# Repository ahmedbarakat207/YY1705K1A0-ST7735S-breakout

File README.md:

# YY1705K1A0 ST7735S 1-Layer Breakout & Driver Library

An open-source, **1-layer single-sided PCB breakout board** and **high-performance C++ driver** for the **YY1705K1A0** 1.8-inch TFT LCD SPI display (ST7735S controller, 128×160 RGB).

---

## Features

- **100% Single-Sided (1-Layer F.Cu)**: Designed specifically for home etching (toner transfer / photoresist). Zero jumpers or bottom vias required.
- **Through-Hole Passives (no SMD soldering)**: R1, R2, R3, C1, C2 are all standard through-hole parts — solder them with any basic iron. The only SMD part is the J2 FPC ZIF connector (required by the display flex cable).
- **Zero DRC Violations**: Optimized trace widths (0.35 mm signals, 0.60 mm power/GND) with 0.30 mm minimum clearances.
- **Clean Silkscreen**: Professional component labeling with open routing corridors.
- **Header-Only C++ Driver (`YY1705K1A0.h`)**:
  - Hardware SPI (fast DMA-capable) and Software bit-bang SPI constructors.
  - Complete 23-color RGB565 palette + `TFT_COLOR(r,g,b)` macro.
  - Fast graphic primitives (pixels, lines, rects, rounded rects, circles, triangles).
  - Built-in 5×7 ASCII font with scaling and Arduino `Print` interface (`print`/`println`).
  - Pre-built UI widgets (`drawProgressBar`).
  - Native support for display sleep, vertical scrolling, rotation (0°–270°), and partial mode.

---

## Hardware Overview

| Parameter | Specification |
|---|---|
| **Display Model** | YY1705K1A0 (1.8" TFT, 128×160) |
| **Driver IC** | Sitronix ST7735S |
| **Board Dimensions** | 34.0 mm × 53.0 mm |
| **Layers** | 1-Layer (Top Copper `F.Cu` Only) |
| **Interface** | 4-Wire SPI (3.3V Logic) |
| **Connectors** | `J1`: 7-Pin 2.54mm Header, `J2`: 12-Pin 0.5mm FPC |

---

## Pinout & Wiring

> **IMPORTANT**: This board and display operate strictly on **3.3V logic**. When interfacing with 5V microcontrollers (e.g. Arduino Uno / Mega), use a logic level shifter.

| J1 Pin | Label | Function | FPC Pin (J2) | MCU Connection (e.g., ESP32 / Arduino) |
|:---:|:---:|---|:---:|---|
| **1** | `+3V3` | +3.3V Power Supply | Pin 10 (`VDD`) | 3.3V Power Out |
| **2** | `GND` | Ground | Pins 2, 4, 11 | GND |
| **3** | `RST` | Reset (Active LOW) | Pin 5 (`RES`) | GPIO (e.g., D8) |
| **4** | `DC` | Data / Command Select | Pin 6 (`A0`) | GPIO (e.g., D9) |
| **5** | `MOSI` | SPI Data (SDA) | Pin 7 (`SDA`) | SPI MOSI (e.g., D11 / GPIO 23) |
| **6** | `SCK` | SPI Clock (SCL) | Pin 8 (`SCL`) | SPI SCK (e.g., D13 / GPIO 18) |
| **7** | `CS` | Chip Select (Active LOW) | Pin 9 (`CS`) | GPIO (e.g., D10 / GPIO 5) |

---

## Bill of Materials (BOM)

| Designator | Description | Package / Footprint | Quantity |
|---|---|---|:---:|
| **J1** | 7-Pin 2.54mm Header Male/Female | 1×07 Pin Header (0.1") THT | 1 |
| **J2** | 12-Pin 0.5mm Pitch Bottom-Contact FPC Connector | SMD 12-Pin 0.5mm **(only SMD part)** | 1 |
| **R1** | 22 Ω Backlight Current Limiter | Axial 1/4W THT, 7.62mm pitch (lying flat) | 1 |
| **R2, R3** | 10 kΩ Pull-up Resistors (`RESET`, `CS`) | Axial 1/4W THT, 5.08mm pitch (vertical mount) | 2 |
| **C1** | 10 µF 10V Ceramic/Electrolytic (Bulk Decoupling) | Disc/Radial THT, 5mm pitch | 1 |
| **C2** | 100 nF (0.1 µF) Ceramic Disc (HF Bypass) | Disc THT, 5mm pitch | 1 |

---

## Quick Start (Arduino / PlatformIO)

### Installation

1. Copy `YY1705K1A0.h` into your Arduino sketch folder or PlatformIO project `include/` directory.
2. In your sketch:

```cpp
#include <SPI.h>
#include "YY1705K1A0.h"

// Define pins
#define TFT_CS    10
#define TFT_DC    9
#define TFT_RST   8

// Hardware SPI instance (Fastest)
YY1705K1A0 tft(TFT_CS, TFT_DC, TFT_RST);

void setup() {
    // Initialize display with standard black-tab profile
    tft.begin(INITR_BLACKTAB);
    tft.fillScreen(TFT_BLACK);

    // Print text
    tft.setTextColor(TFT_WHITE, TFT_BLACK);
    tft.drawString(10, 20, "Hello World!", TFT_YELLOW, TFT_BLACK, 2);

    // Draw UI shapes
    tft.drawRoundRect(10, 60, 108, 30, 4, TFT_CYAN);
    tft.drawProgressBar(10, 100, 108, 14, 75, TFT_GREEN, TFT_DARKGREY, TFT_WHITE);
}

void loop() {
}
```

---

## DIY PCB Fabrication (Toner Transfer)

Print-ready vector PDF files scaled at 1:1 for DIY etching:

- **[YY1705K1A0_breakout_scaled_landscape.pdf](YY1705K1A0_breakout_scaled_landscape.pdf)**: 2 scaled boards per A4 page.
- **[YY1705K1A0_breakout_scaled_landscape_mirrored.pdf](YY1705K1A0_breakout_scaled_landscape_mirrored.pdf)**: Mirrored for direct iron-on toner transfer.

> **Printing Note**: Print with **Scale: 100% / Actual Size** enabled in your PDF viewer.

---

## Repository Structure

```
├── README.md                                          # Project documentation
├── LICENSE                                            # MIT Open-Source License
├── library.properties                                 # Arduino Library descriptor
├── library.json                                       # PlatformIO Library descriptor
├── YY1705K1A0.h                                       # Display driver header library
├── YY1705K1A0_breakout.kicad_pro                      # KiCad project file
├── YY1705K1A0_breakout.kicad_sch                      # KiCad schematic
├── YY1705K1A0_breakout.kicad_pcb                      # KiCad 1-layer PCB layout
├── BOM.csv                                            # Bill of Materials
├── display_connector_pinout.csv                       # FPC 12-pin reference sheet
├── WIRING_GUIDE.md                                    # Detailed wiring instructions
├── YY1705K1A0_breakout_scaled_landscape.pdf           # Printable A4 etching mask
├── YY1705K1A0_breakout_scaled_landscape_mirrored.pdf  # Mirrored etching mask
└── examples/
    └── GraphicTest/
        └── GraphicTest.ino                            # Complete demo sketch
```

---

## License

This project is open-source hardware and software licensed under the [MIT License](LICENSE).

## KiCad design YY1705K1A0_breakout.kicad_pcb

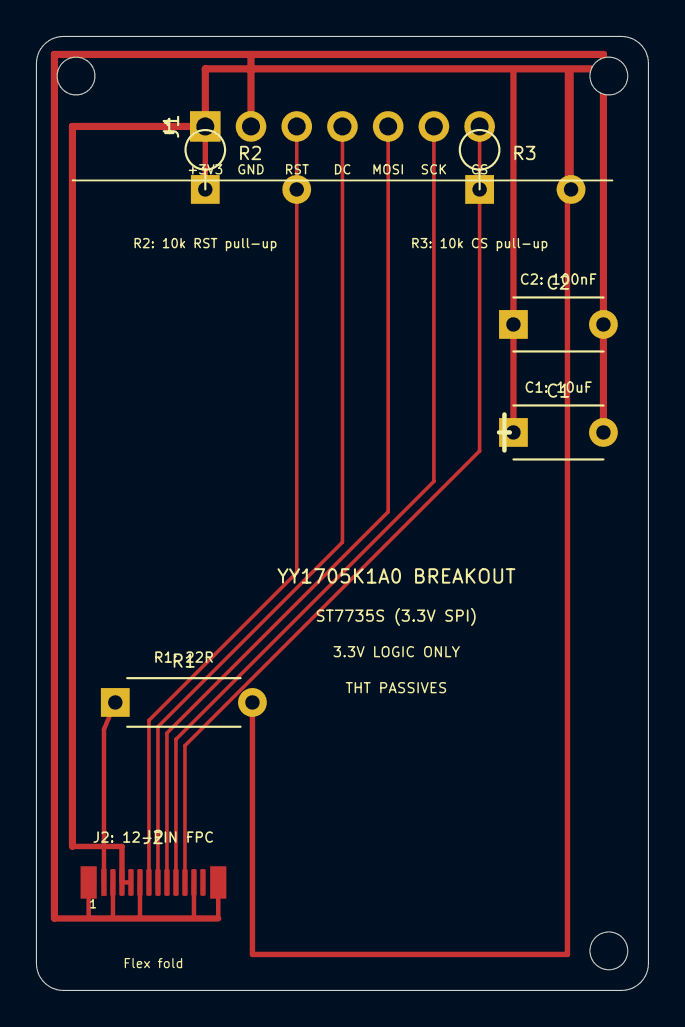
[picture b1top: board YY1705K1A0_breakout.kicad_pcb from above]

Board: 2 copper layers, 34.0 x 53.0 mm, 10 parts (0 on the bottom side), 8 nets.

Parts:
C1: 10uF; C_Disc_D5.0mm_W2.5mm_P5.00mm
C2: 100nF; C_Disc_D5.0mm_W2.5mm_P5.00mm
H1, H2, H3: MountingHole_2.1mm
J1: CONN_7PIN; PinHeader_1x07_P2.54mm
J2: FPC_12P_0.5mm; FPC_12_0.5mm
R1: 22R; R_Axial_DIN0207_L6.3mm_D2.5mm_P7.62mm_Horizontal
R2, R3: 10k; R_Axial_DIN0207_L6.3mm_D2.5mm_P5.08mm_Vertical

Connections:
+3V3: C1.1, C2.1, J1.1, J2.3, J2.4, R1.2, R2.1, R3.2
CS: J1.7, J2.10, R3.1
DC_A0: J1.4, J2.7
GND: C1.2, C2.2, J1.2, J2.2, J2.5, J2.11, J2.MP
LEDA_SUPPLY: J2.1, R1.1
RESET: J1.3, J2.6, R2.2
SCL_SCK: J1.6, J2.9
SDA_MOSI: J1.5, J2.8
